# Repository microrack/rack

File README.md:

# rack
Motherboard with power and base audio output for synth modules

## Mechanical specifications

* module height
* supply placings
* mount holes

## Mechanical recommendations

* module width as small as possible
* height of controls
* minimal distance between controls

## Electrical specifications

* Supply voltage: ±9 volt, ±5%
* Maximum supply current: 500 mA @ -9V / 1000 mA @ +9V (it is total maximum current of all modules)
* Recommended supply current: 50 mA @ -9 V / 50 mA @ -9V

## Electrical recommendations (for interconnect)

### Input
* High impedance input (1kOhm typ.)
* Many inputs (sum), many outpus (parallel)
* Use terminator on inputs to prevent change level on connect new source
* Adjustable level of input (common only)

Adjustable sum input example (note: this schematic invert input signal):

Non-adjustable and noninverting input schematic (you can add optional potentiometer next):

### Output
* Protect outputs with resistors (100 ohm typ.)
* Low impedance output (100 ohm typ.)
* Adjust level of output, common only

* Use attenuverter for CV outputs

### Power supply

* use linear regulator for power supply
* Use ±5V internal supply voltage
* Do not forget to add blocking capacitors close to the IC

### Signal level considerations
* 5V gate
* 1 V/oct CV
* 5 Vpp linear level (0 dB)

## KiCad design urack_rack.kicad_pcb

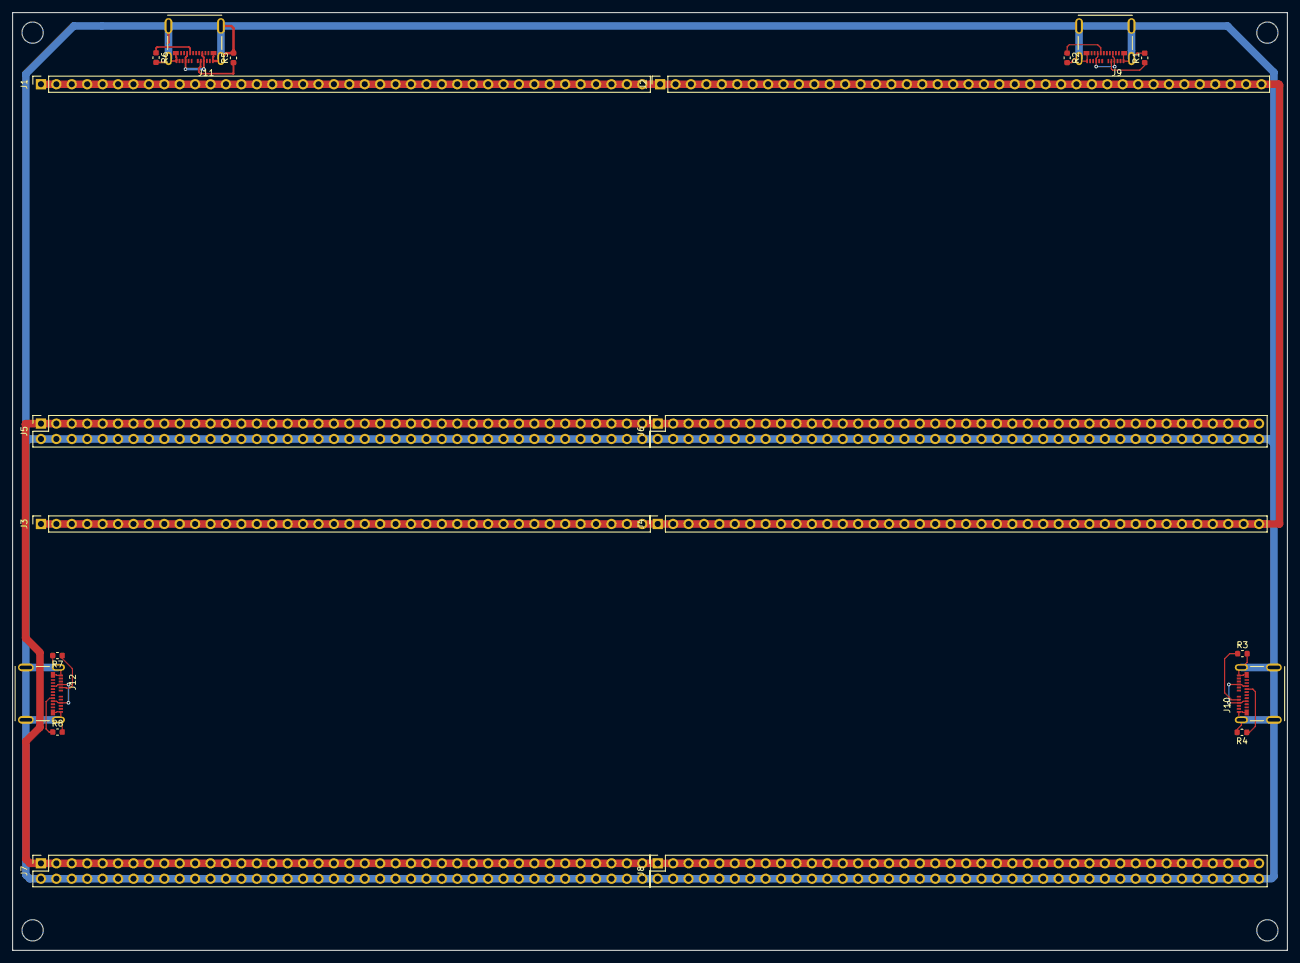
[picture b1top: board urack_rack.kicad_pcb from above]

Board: 2 copper layers, 210.0 x 154.5 mm, 20 parts (0 on the bottom side), 12 nets.

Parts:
J1, J2, J3, J4: Conn_01x40; pbd1x40
J5, J6, J7, J8: Conn_02x40_Odd_Even; pbd2x40
J9, J10, J11, J12: 105450-0101; MOLEX_105450-0101
R1, R2, R3, R4, R5, R6, R7, R8: 5K1; r0603

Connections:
+5V: J9.A4, J9.A9, J9.B4, J9.B9, J10.A4, J10.A9, J10.B4, J10.B9, J11.A4, J11.A9, J11.B4, J11.B9, J12.A4, J12.A9, J12.B4, J12.B9
+9V: J1.1, J1.2, J1.3, J1.4, J1.5, J1.6, J1.7, J1.8, J1.9, J1.10, J1.11, J1.12, J1.13, J1.14, J1.15, J1.16, J1.17, J1.18, J1.19, J1.20, J1.21, J1.22, J1.23, J1.24, J1.25, J1.26, J1.27, J1.28, J1.29, J1.30, J1.31, J1.32, J1.33, J1.34, J1.35, J1.36, J1.37, J1.38, J1.39, J1.40, J2.1, J2.2, J2.3, J2.4, J2.5, J2.6, J2.7, J2.8, J2.9, J2.10, J2.11, J2.12, J2.13, J2.14, J2.15, J2.16, J2.17, J2.18, J2.19, J2.20, J2.21, J2.22, J2.23, J2.24, J2.25, J2.26, J2.27, J2.28, J2.29, J2.30, J2.31, J2.32, J2.33, J2.34, J2.35, J2.36, J2.37, J2.38, J2.39, J2.40, J3.1, J3.2, J3.3, J3.4, J3.5, J3.6, J3.7, J3.8, J3.9, J3.10, J3.11, J3.12, J3.13, J3.14, J3.15, J3.16, J3.17, J3.18, J3.19, J3.20, J3.21, J3.22, J3.23, J3.24, J3.25, J3.26, J3.27, J3.28, J3.29, J3.30, J3.31, J3.32, J3.33, J3.34, J3.35, J3.36, J3.37, J3.38, J3.39, J3.40, J4.1, J4.2, J4.3, J4.4, J4.5, J4.6, J4.7, J4.8, J4.9, J4.10, J4.11, J4.12, J4.13, J4.14, J4.15, J4.16, J4.17, J4.18, J4.19, J4.20, J4.21, J4.22, J4.23, J4.24, J4.25, J4.26, J4.27, J4.28, J4.29, J4.30, J4.31, J4.32, J4.33, J4.34, J4.35, J4.36, J4.37, J4.38, J4.39, J4.40
-9V: J5.1, J5.3, J5.5, J5.7, J5.9, J5.11, J5.13, J5.15, J5.17, J5.19, J5.21, J5.23, J5.25, J5.27, J5.29, J5.31, J5.33, J5.35, J5.37, J5.39, J5.41, J5.43, J5.45, J5.47, J5.49, J5.51, J5.53, J5.55, J5.57, J5.59, J5.61, J5.63, J5.65, J5.67, J5.69, J5.71, J5.73, J5.75, J5.77, J5.79, J6.1, J6.3, J6.5, J6.7, J6.9, J6.11, J6.13, J6.15, J6.17, J6.19, J6.21, J6.23, J6.25, J6.27, J6.29, J6.31, J6.33, J6.35, J6.37, J6.39, J6.41, J6.43, J6.45, J6.47, J6.49, J6.51, J6.53, J6.55, J6.57, J6.59, J6.61, J6.63, J6.65, J6.67, J6.69, J6.71, J6.73, J6.75, J6.77, J6.79, J7.1, J7.3, J7.5, J7.7, J7.9, J7.11, J7.13, J7.15, J7.17, J7.19, J7.21, J7.23, J7.25, J7.27, J7.29, J7.31, J7.33, J7.35, J7.37, J7.39, J7.41, J7.43, J7.45, J7.47, J7.49, J7.51, J7.53, J7.55, J7.57, J7.59, J7.61, J7.63, J7.65, J7.67, J7.69, J7.71, J7.73, J7.75, J7.77, J7.79, J8.1, J8.3, J8.5, J8.7, J8.9, J8.11, J8.13, J8.15, J8.17, J8.19, J8.21, J8.23, J8.25, J8.27, J8.29, J8.31, J8.33, J8.35, J8.37, J8.39, J8.41, J8.43, J8.45, J8.47, J8.49, J8.51, J8.53, J8.55, J8.57, J8.59, J8.61, J8.63, J8.65, J8.67, J8.69, J8.71, J8.73, J8.75, J8.77, J8.79
GND: J5.2, J5.4, J5.6, J5.8, J5.10, J5.12, J5.14, J5.16, J5.18, J5.20, J5.22, J5.24, J5.26, J5.28, J5.30, J5.32, J5.34, J5.36, J5.38, J5.40, J5.42, J5.44, J5.46, J5.48, J5.50, J5.52, J5.54, J5.56, J5.58, J5.60, J5.62, J5.64, J5.66, J5.68, J5.70, J5.72, J5.74, J5.76, J5.78, J5.80, J6.2, J6.4, J6.6, J6.8, J6.10, J6.12, J6.14, J6.16, J6.18, J6.20, J6.22, J6.24, J6.26, J6.28, J6.30, J6.32, J6.34, J6.36, J6.38, J6.40, J6.42, J6.44, J6.46, J6.48, J6.50, J6.52, J6.54, J6.56, J6.58, J6.60, J6.62, J6.64, J6.66, J6.68, J6.70, J6.72, J6.74, J6.76, J6.78, J6.80, J7.2, J7.4, J7.6, J7.8, J7.10, J7.12, J7.14, J7.16, J7.18, J7.20, J7.22, J7.24, J7.26, J7.28, J7.30, J7.32, J7.34, J7.36, J7.38, J7.40, J7.42, J7.44, J7.46, J7.48, J7.50, J7.52, J7.54, J7.56, J7.58, J7.60, J7.62, J7.64, J7.66, J7.68, J7.70, J7.72, J7.74, J7.76, J7.78, J7.80, J8.2, J8.4, J8.6, J8.8, J8.10, J8.12, J8.14, J8.16, J8.18, J8.20, J8.22, J8.24, J8.26, J8.28, J8.30, J8.32, J8.34, J8.36, J8.38, J8.40, J8.42, J8.44, J8.46, J8.48, J8.50, J8.52, J8.54, J8.56, J8.58, J8.60, J8.62, J8.64, J8.66, J8.68, J8.70, J8.72, J8.74, J8.76, J8.78, J8.80, J9.A1, J9.A12, J9.B1, J9.B12, J9.S1, J9.S2, J9.S3, J9.S4, J10.A1, J10.A12, J10.B1, J10.B12, J10.S1, J10.S2, J10.S3, J10.S4, J11.A1, J11.A12, J11.B1, J11.B12, J11.S1, J11.S2, J11.S3, J11.S4, J12.A1, J12.A12, J12.B1, J12.B12, J12.S1, J12.S2, J12.S3, J12.S4, R1.2, R2.2, R3.2, R4.2, R5.2, R6.2, R7.2, R8.2
unnamed: J9.A5, R1.1
unnamed: J9.B5, R2.1
unnamed: J10.A5, R3.1
unnamed: J10.B5, R4.1
unnamed: J11.A5, R5.1
unnamed: J11.B5, R6.1
unnamed: J12.A5, R7.1
unnamed: J12.B5, R8.1

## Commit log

2019-02-04 init
2019-02-08 add extension mount
2019-02-16 add kikcad project
2019-03-08 some old changes
2019-03-08 rename pcb folder
2019-03-08 update pcb
2019-03-16 add some picture for spec
2019-03-16 update attenuverter image
2019-03-16 shithub update
2019-03-16 shithub update 1
2019-03-16 next shithub update
2019-03-31 update rack from legacy repo
2019-03-31 add example lib path files and gitignore
2019-03-31 remove old pcb files
2019-04-05 Исправленны абсолютные пути на отнасительные
2019-04-05 Исправленны пути к библиотекам проекта.
2020-11-02 Add linear voltage reguator make PCB
2020-11-02 update gitignore
2020-11-02 remove local fp/sym lib table
2020-11-02 remove cache
2020-11-28 New version PCB. Change power connectors, add USB Type C connector Molex 105450-0101
2020-11-29 board dimensions changed
